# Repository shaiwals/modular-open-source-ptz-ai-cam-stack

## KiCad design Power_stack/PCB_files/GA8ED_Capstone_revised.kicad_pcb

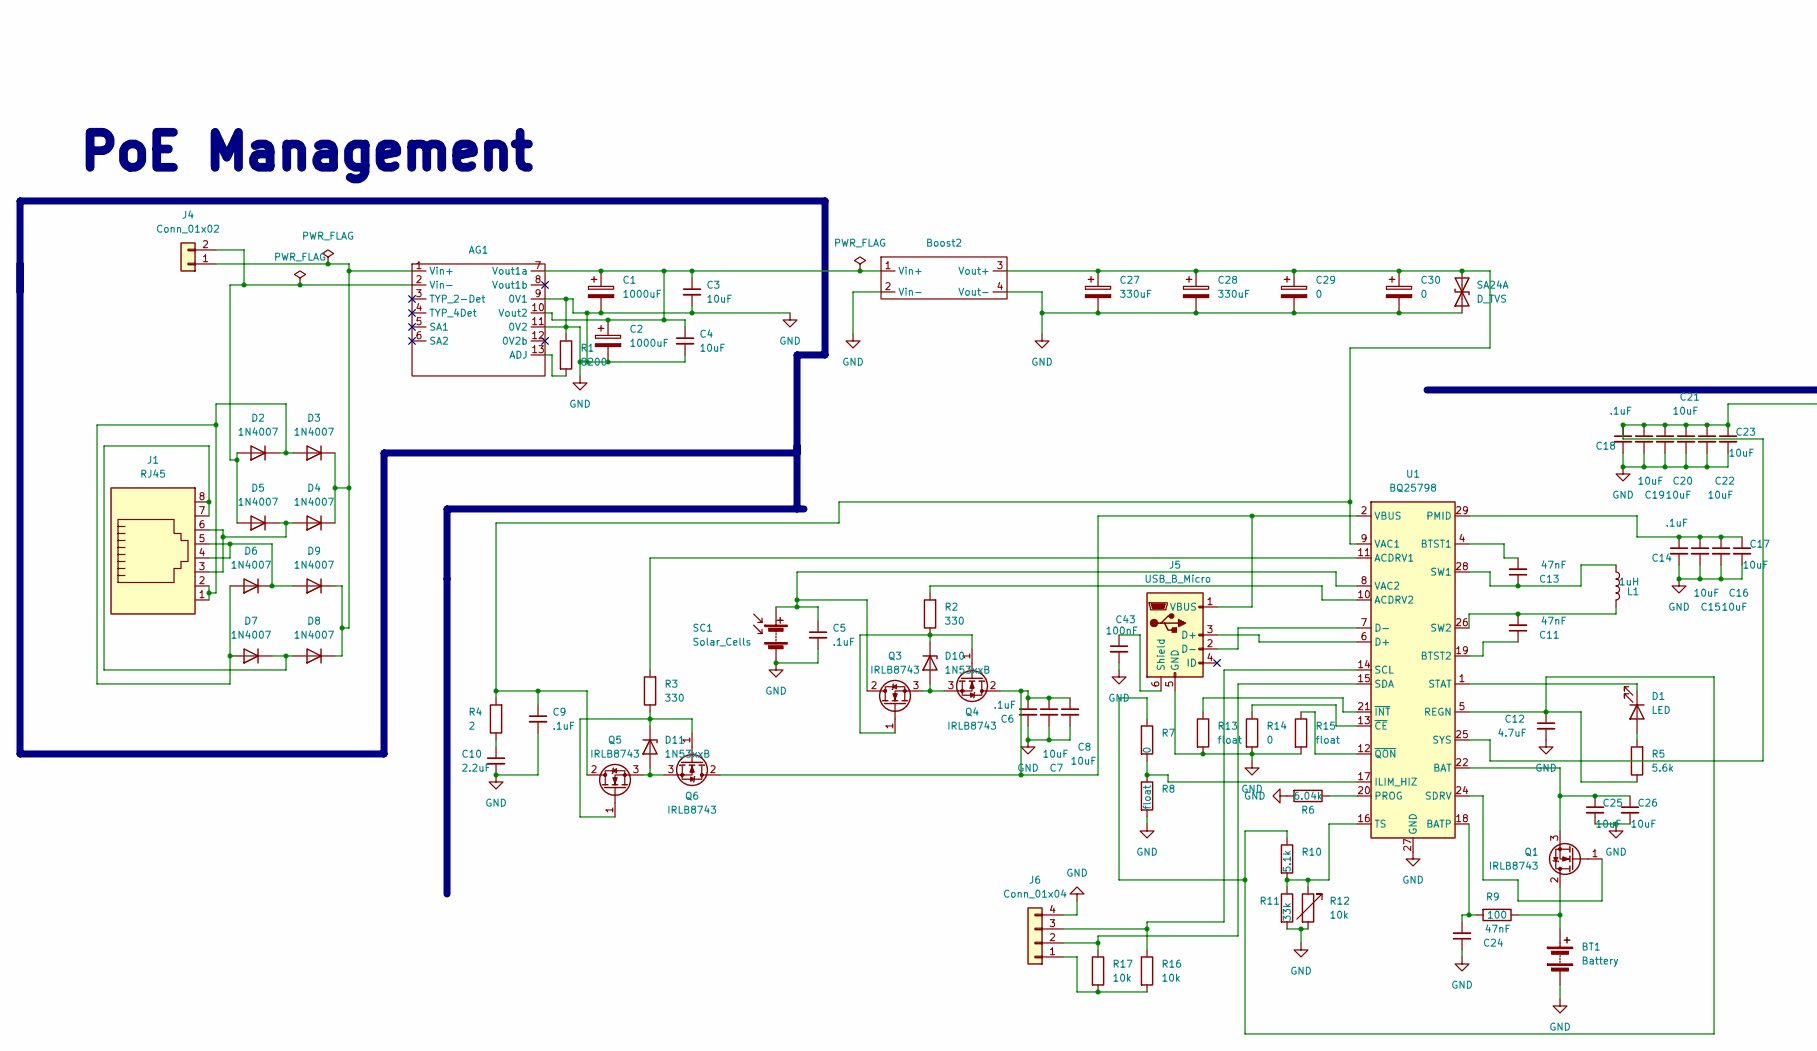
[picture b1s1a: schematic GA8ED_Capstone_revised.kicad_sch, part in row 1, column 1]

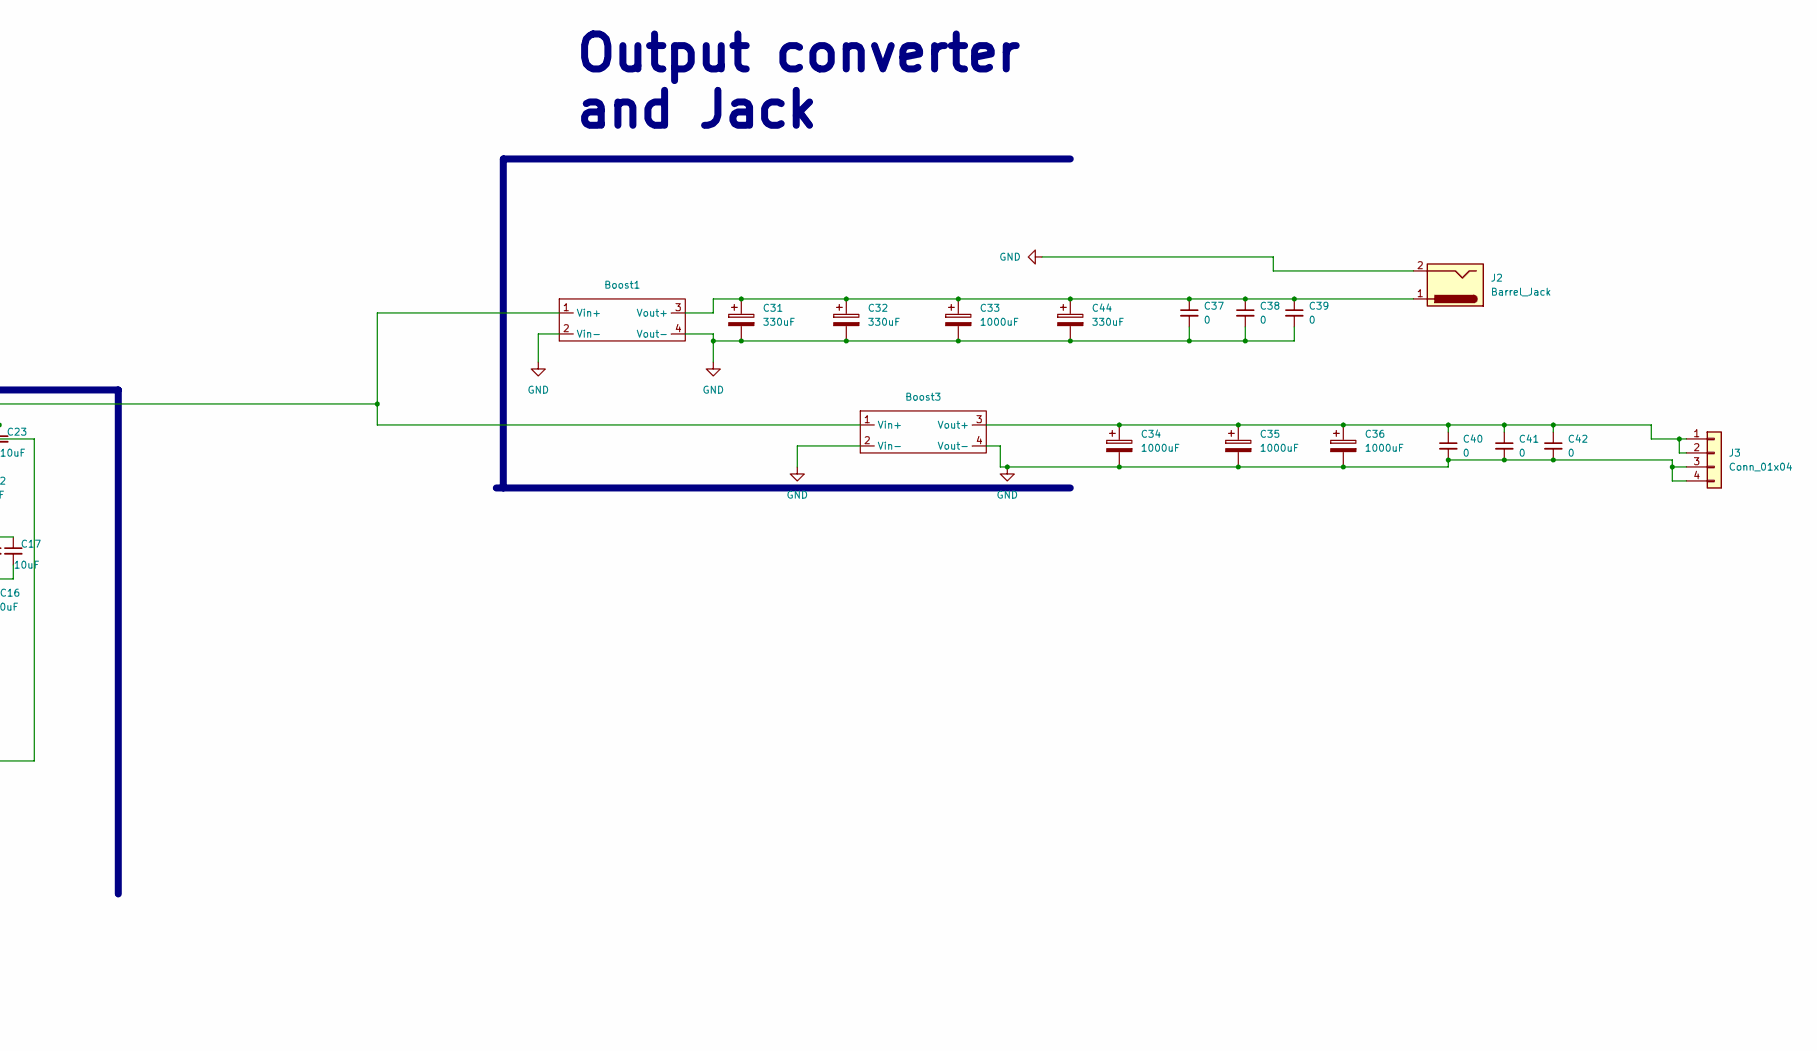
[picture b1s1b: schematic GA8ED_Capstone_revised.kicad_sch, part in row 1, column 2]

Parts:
AG1: Converter_DCDC_Silvertel_Ag5810
BT1: Battery; TerminalBlock_Xinya_XY308-2.54-2P_1x02_P2.54mm_Horizontal
Boost1, Boost2: boost_1
Boost3: buck1
C1, C2, C33, C34, C35, C36: 1000uF; CP_Radial_D14.0mm_P5.00mm
C3, C4, C7, C8, C15, C16, C17, C19, C20, C21, C22, C23, C25, C26: 10uF; C_Disc_D5.0mm_W2.5mm_P5.00mm
C5, C6, C9, C14, C18: .1uF; C_Disc_D5.0mm_W2.5mm_P5.00mm
C10: 2.2uF; C_Disc_D5.0mm_W2.5mm_P5.00mm
C11, C13, C24: 47nF; C_Disc_D5.0mm_W2.5mm_P5.00mm
C12: 4.7uF; C_Disc_D5.0mm_W2.5mm_P5.00mm
C27, C28, C31, C32, C44: 330uF; CP_Radial_D14.0mm_P5.00mm
C29, C30, C37, C38, C39, C40, C41, C42: 0; C_Disc_D5.0mm_W2.5mm_P5.00mm
C43: 100nF; C_Disc_D5.0mm_W2.5mm_P5.00mm
D1: LED; LED_D5.0mm_IRBlack
D2, D3, D4, D5, D6, D7, D8, D9: 1N4007; D_DO-41_SOD81_P10.16mm_Horizontal
D10, D11: 1N53xxB; D_DO-201_P15.24mm_Horizontal
J1: RJ45; PinHeader_1x08_P2.54mm_Horizontal
J2: Barrel_Jack; TerminalBlock_MaiXu_MX126-5.0-02P_1x02_P5.00mm
J3, J6: Conn_01x04; PinHeader_1x04_P2.54mm_Horizontal
J4: Conn_01x02; PinSocket_1x02_P2.54mm_Horizontal
J5: USB_B_Micro; USB_Micro-B_Amphenol_10103594-0001LF_Horizontal
L1: 1uH; L_Radial_D16.8mm_P12.07mm_Vishay_IHB-1
Q1, Q3, Q4, Q5, Q6: IRLB8743; TO-220-3_Vertical
R1: 8200; R_Axial_DIN0207_L6.3mm_D2.5mm_P7.62mm_Horizontal
R2, R3: 330; R_Axial_DIN0207_L6.3mm_D2.5mm_P7.62mm_Horizontal
R4: 2; R_Axial_DIN0207_L6.3mm_D2.5mm_P7.62mm_Horizontal
R5: 5.6k; R_Axial_DIN0207_L6.3mm_D2.5mm_P7.62mm_Horizontal
R6: 6.04k; R_Axial_DIN0207_L6.3mm_D2.5mm_P7.62mm_Horizontal
R7, R14: 0; R_Axial_DIN0207_L6.3mm_D2.5mm_P7.62mm_Horizontal
R8, R13, R15: float; R_Axial_DIN0207_L6.3mm_D2.5mm_P7.62mm_Horizontal
R9: 100; R_Axial_DIN0207_L6.3mm_D2.5mm_P7.62mm_Horizontal
R10: 5.1k; R_Axial_DIN0207_L6.3mm_D2.5mm_P7.62mm_Horizontal
R11: 33k; R_Axial_DIN0207_L6.3mm_D2.5mm_P7.62mm_Horizontal
R12, R16, R17: 10k; R_Axial_DIN0207_L6.3mm_D2.5mm_P7.62mm_Horizontal
SA24A: D_TVS
SC1: Solar_Cells; TerminalBlock_MaiXu_MX126-5.0-02P_1x02_P5.00mm
U1: BQ25798; Texas_RQM0029A_VQFN-29_4x4mm_P0.4mm

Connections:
GND: AG1.9 (0V1), AG1.11 (0V2), BT1.2 (-), Boost1.2 (Vin-), Boost1.4 (Vout-), Boost2.2 (Vin-), Boost2.4 (Vout-), Boost3.2 (Vin-), Boost3.4 (Vout-), C1.2, C2.2, C3.2, C4.2, C5.2, C6.2, C7.2, C8.2, C9.2, C10.2, C12.2, C14.2, C15.2, C16.2, C17.2, C18.2, C19.2, C20.2, C21.2, C22.2, C23.2, C24.1, C25.2, C26.2, C27.2, C28.2, C29.2, C30.2, C31.2, C32.2, C33.2, C34.2, C35.2, C36.2, C37.2, C38.2, C39.2, C40.2, C41.2, C42.2, C43.2, C44.2, J2.2, J3.3, J3.4, J5.5 (GND), J6.4, R1.1, R6.2, R8.2, R11.2, R12.2, R13.2, R14.2, R15.2, SA24A.1 (A1), SC1.2 (-), U1.27 (GND)
unnamed: AG1.13 (ADJ), R1.2
unnamed: AG1.1 (Vin+), D3.1 (K), D4.1 (K), D8.1 (K), D9.1 (K), J4.1
unnamed: AG1.2 (Vin-), D2.2 (A), D5.2 (A), J4.2
unnamed: AG1.7 (Vout1a), AG1.10 (Vout2), Boost2.1 (Vin+), C1.1, C2.1, C3.1, C4.1
unnamed: BT1.1 (+), Q1.2 (D), R9.1
unnamed: Boost1.1 (Vin+), Boost3.1 (Vin+), C18.1, C19.1, C20.1, C21.1, C22.1, C23.1, U1.25 (SYS)
unnamed: Boost1.3 (Vout+), C31.1, C32.1, C33.1, C37.1, C38.1, C39.1, C44.1, J2.1
unnamed: Boost2.3 (Vout+), C9.1, C27.1, C28.1, C29.1, C30.1, Q5.2 (D), R4.2, SA24A.2 (A2), U1.9 (VAC1)
unnamed: Boost3.3 (Vout+), C34.1, C35.1, C36.1, C40.1, C41.1, C42.1, J3.1, J3.2
unnamed: C10.1, R4.1
unnamed: D1.2 (A), R5.2
unnamed: D1.1 (K), U1.1 (STAT)
unnamed: D2.1 (K), D3.2 (A), D6.2 (A), D7.2 (A), J1.1, J1.2
unnamed: D4.2 (A), D5.1 (K), J1.3, J1.6
unnamed: D6.1 (K), D9.2 (A), J1.4, J1.5
unnamed: D7.1 (K), D8.2 (A), J1.7, J1.8
unnamed: D10.2 (A), Q3.3 (S), Q4.3 (S)
unnamed: D10.1 (K), Q3.1 (G), Q4.1 (G), R2.1
unnamed: D11.2 (A), Q5.3 (S), Q6.3 (S)
unnamed: D11.1 (K), Q5.1 (G), Q6.1 (G), R3.1
unnamed: J5.3 (D+), U1.6 (D+)
unnamed: J5.2 (D-), U1.7 (D-)
unnamed: C43.1, J5.6 (Shield)
unnamed: C6.1, C7.1, C8.1, J5.1 (VBUS), Q4.2 (D), Q6.2 (D), U1.2 (VBUS), U1.3 (VBUS)
unnamed: J6.1, R16.2, R17.2
unnamed: J6.2, R17.1, U1.15 (SDA)
unnamed: J6.3, R16.1, U1.14 (SCL)
unnamed: Q1.1 (G), U1.24 (SDRV)
unnamed: C25.1, C26.1, Q1.3 (S), U1.22 (BAT), U1.23 (BAT)
unnamed: C5.1, Q3.2 (D), SC1.1 (+), U1.8 (VAC2)
unnamed: R3.2, U1.11 (ACDRV1)
unnamed: R2.2, U1.10 (ACDRV2)
unnamed: C24.2, R9.2, U1.18 (BATP)
unnamed: C13.2, U1.4 (BTST1)
unnamed: C11.1, U1.19 (BTST2)
unnamed: R7.2, R8.1, U1.17 (ILIM_HIZ)
unnamed: C14.1, C15.1, C16.1, C17.1, U1.29 (PMID)
unnamed: R6.1, U1.20 (PROG)
unnamed: C12.1, R5.1, R7.1, R10.1, U1.5 (REGN)
unnamed: C13.1, L1.1, U1.28 (SW1)
unnamed: C11.2, L1.2, U1.26 (SW2)
unnamed: R10.2, R11.1, R12.1, U1.16 (TS)
unnamed: R14.1, U1.13 (~CE)
unnamed: R13.1, U1.21 (~INT)
unnamed: R15.1, U1.12 (~QON)

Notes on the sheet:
Output converter and Jack
PoE Management

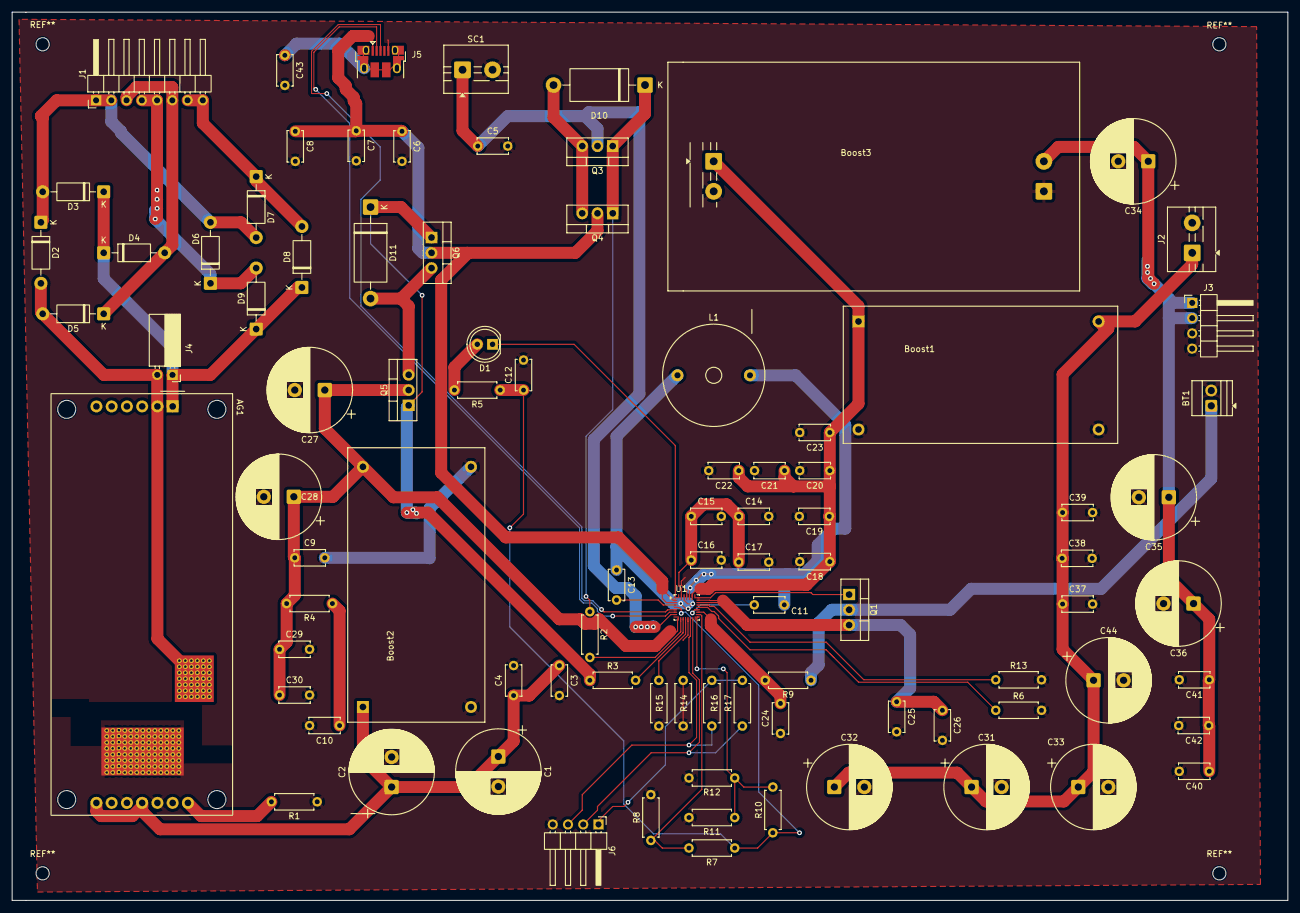
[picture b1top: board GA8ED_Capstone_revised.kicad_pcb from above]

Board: 2 copper layers, 212.5 x 148.0 mm, 91 parts (0 on the bottom side), 46 nets.

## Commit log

2026-06-02 adding original power stack files
2026-06-05 Add NPU accelerated YOLO object detection pipeline
